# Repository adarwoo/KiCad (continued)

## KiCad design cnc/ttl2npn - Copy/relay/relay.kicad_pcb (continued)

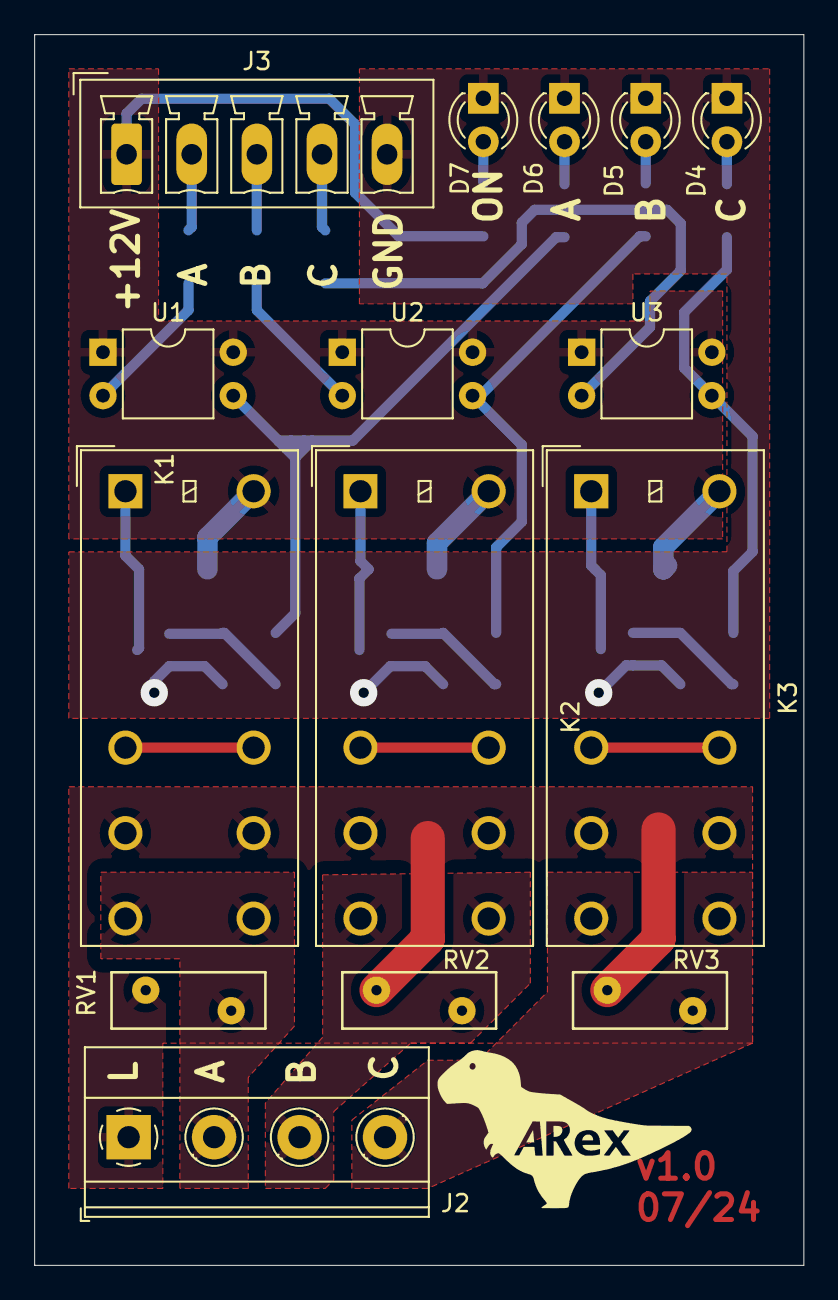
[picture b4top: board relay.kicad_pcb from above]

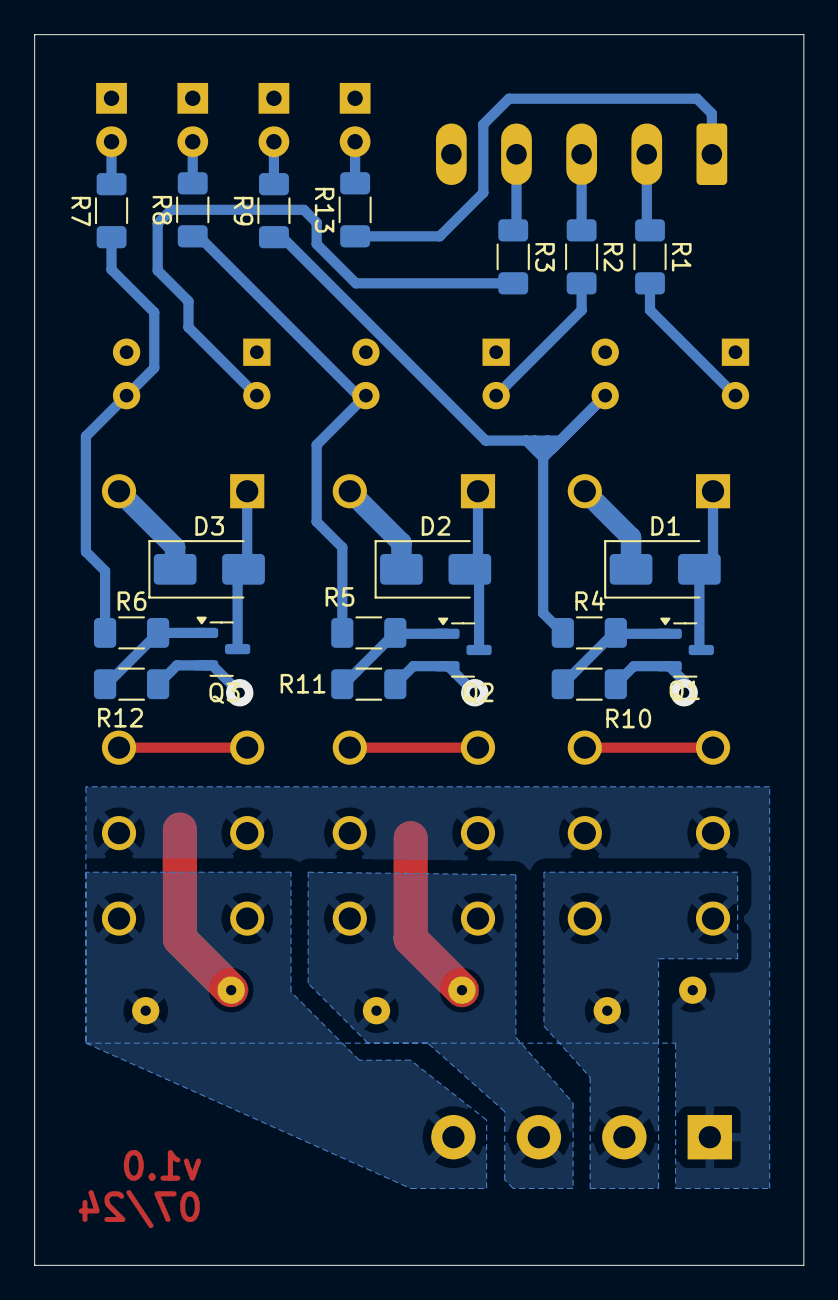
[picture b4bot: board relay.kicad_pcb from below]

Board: 2 copper layers, 45.0 x 72.0 mm, 34 parts (19 on the bottom side), 25 nets.
